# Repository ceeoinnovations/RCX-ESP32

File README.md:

# RCX-ESP32

A browser-based tool for programming LEGO RCX using an ESP32 as an IR
transmitter. Write MicroPython in the browser, flash it to the ESP32 over
WebSerial, and control the RCX over IR — no software to install.

Live site: https://ceeoinnovations.github.io/RCX-ESP32/

---

## What You Need

- An ESP32 (tested on ESP32-C6)
- A LEGO RCX 2.0 brick with fresh batteries
- An IR LED wired to GPIO 2 of the ESP32 (see wiring below)
- Chrome or Edge browser (WebSerial and Web Bluetooth require Chromium)
- A USB cable to connect the ESP32 to your computer

---

## Wiring the IR LED

The ESP32 drives an IR LED through an NPN transistor so it has enough current to
reach the RCX. A PCB can be used based on the files in `docs/KiCad`, or you can
wire it up on a breadboard.

```
ESP32 GPIO 2 ──── 330Ω ──── Base (PN2222A)
                             Collector ──── IR LED (anode) ──── 3.3V
                             Emitter  ──── GND
                             IR LED cathode ──── GND
```

---

## First Time Setup

**1. Open the app** Go to https://ceeoinnovations.github.io/RCX-ESP32/ in
Chrome.

**2. Connect your ESP32** Click **connect up** in the Serial Terminal panel.
Select your ESP32's COM port from the browser dialog.

**3. Install the RCX library** Click **Install RCX Lib**. This uploads the RCX
driver files to the ESP32 filesystem. You only need to do this once per board.

**4. Load a template** Pick a template from the dropdown in the right panel
(e.g. Beep Test) and click **Load Template**. The code will appear in the
editor.

**5. Run it** Click **run** to execute the code on the ESP32. Point the IR LED
at the RCX — if wired correctly the RCX should respond.

---

## USB Tower Mode

If you have the original LEGO USB IR Tower you can plug it directly into your
computer and control the RCX without an ESP32 at all.

**Setup:**

1. Plug the USB tower into your computer
2. In the right panel switch to **USB Tower** mode
3. Click **Connect Tower** and select the tower from the browser's USB device
   picker
4. Use the quick action buttons (Ping, Beep, Stop) or load a tower template and
   click **Run on Tower**

The tower templates use `await rcx.*` syntax and run entirely in the browser —
no serial connection needed.

---

## BLE Control (Tech Element Mode)

The ESP32 can also act as a Bluetooth tech element, receiving commands from the
browser over BLE and sending them to the RCX over IR.

**Setup:**

1. Click **Load TE Files** to upload the BLE tech element files to the ESP32
2. The editor will load `main_code.py` — click **run** to start advertising
3. In the right panel, click **Connect** under BLE Control
4. Select the device named **Maria** from the browser's Bluetooth picker
5. Use the command dropdown to send commands to the RCX over BLE

---

## Future Work

- Add more Python support for the LASM opcodes
- Add support for LASM compiled bytecode (currently only raw opcodes)
- Add program download to RCX (currently only live commands)

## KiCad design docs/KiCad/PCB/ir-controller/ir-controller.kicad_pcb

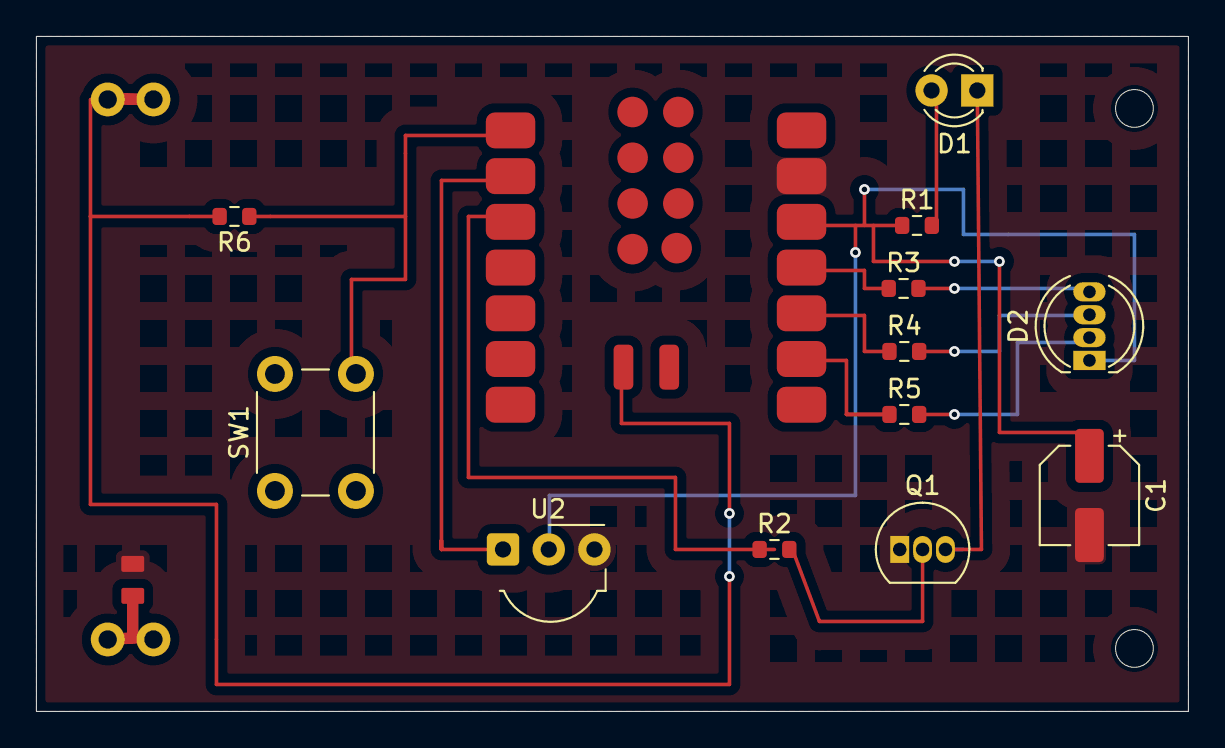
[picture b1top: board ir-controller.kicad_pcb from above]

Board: 2 copper layers, 64.0 x 37.5 mm, 18 parts (0 on the bottom side), 16 nets.

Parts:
C1: C; CP_Elec_5x5.8
D1: IR204A; LED_D3.0mm_IRBlack
D2: LED_ARGB; LED_D5.0mm-4_RGB
DIODE0: CLEAR-BLUE-0805; LED-0805_8004780
POGON1, POGON2: 1X01_513
POGOP1, POGOP2: 1X01_513
Q1: PN2222A; TO-92_Inline
R1, R2, R3, R4, R5, R6: 10; R_0603_1608Metric
SW1: SW_Push_Dual; SW_PUSH_6mm
U1: MOUDLE-SEEEDUINO-XIAO-ESP32C3; XIAO-ESP32C6-SMD
U2: TSOP21xx; Vishay_MOLD-3Pin

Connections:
GND: C1.2, DIODE0.+, Q1.1 (E), U1.13 (GND), U2.3 (GND)
GNDTER: DIODE0.-, POGON1.1, POGON2.1
unnamed: D1.2 (A), R1.2
unnamed: D1.1 (K), Q1.3 (C)
unnamed: C1.1, D2.1 (A), R1.1, U1.12 (3V3), U2.2 (Vs)
unnamed: D2.4 (BK), R3.2
unnamed: D2.3 (GK), R4.2
unnamed: D2.2 (RK), R5.2
unnamed: Q1.2 (B), R2.2
unnamed: R6.1, SW1.2, U1.1 (PA02_A0_D0)
unnamed: U1.2 (PA4_A1_D1), U2.1 (OUT)
unnamed: R4.1, U1.10 (PA5_A9_D9_MISO)
unnamed: R3.1, U1.11 (PA6_A10_D10_MOSI)
unnamed: R5.1, U1.9 (PA7_A8_D8_SCK)
unnamed: R2.1, U1.3 (PA10_A2_D2)
POS: POGOP1.1, POGOP2.1

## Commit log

2026-05-07 new repo
2026-05-08 bug fixes
2026-05-08 modified readme
2026-05-08 added docs
2026-05-08 added pcb docs
2026-05-08 file strcture changes
2026-05-08 reference notes changes
2026-05-08 readme
2026-05-08 future work section
